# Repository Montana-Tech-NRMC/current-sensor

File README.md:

Current Sensor

Daughter board to measure current to the motors. Kept separate from the remex for protection.

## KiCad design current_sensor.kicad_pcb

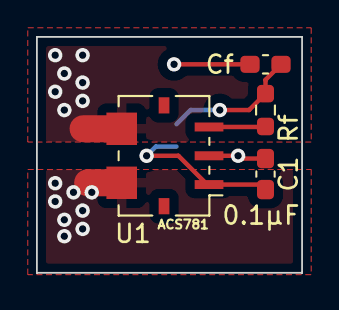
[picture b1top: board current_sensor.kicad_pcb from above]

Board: 2 copper layers, 14.7 x 13.1 mm, 5 parts (1 on the bottom side), 4 nets.

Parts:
C1: 0.1 uF; C_0603_1608Metric_Pad1.08x0.95mm_HandSolder
Cf: Cf; C_0603_1608Metric_Pad1.08x0.95mm_HandSolder
J3: Conn_01x03_Male; Molex_PicoBlade_53261-0371_1x03-1MP_P1.25mm_Horizontal
Rf: Rf; R_0603_1608Metric_Pad0.98x0.95mm_HandSolder
U1: ACS781xLRTR-100B; Allegro_PSOF-7_4.8x6.4mm_P1.60mm

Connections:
+3.3V: C1.1, J3.2, U1.1 (VCC)
GNDREF: C1.2, Cf.2, J3.3, U1.2 (GND)
unnamed: Cf.1, J3.1, Rf.2
unnamed: Rf.1, U1.3 (VOUT)

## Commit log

2022-12-03 init
2022-12-03 README
2023-01-26 making it much smaller
2023-01-28 make it smaller
2023-01-28 revision bump
2023-01-28 update the readme
2023-02-02 make trace bigger
2023-02-17 hopefully this makes copper be copper
2023-02-18 symmetry
2023-02-18 label the cap
